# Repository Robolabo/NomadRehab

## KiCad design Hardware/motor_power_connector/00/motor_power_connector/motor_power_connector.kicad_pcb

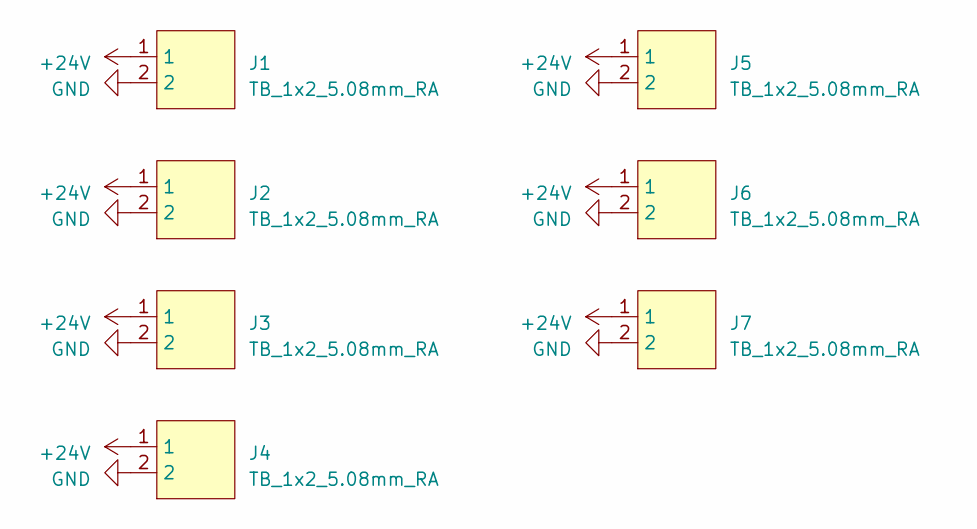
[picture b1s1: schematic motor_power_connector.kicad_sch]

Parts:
J1, J2, J3, J4, J5, J6, J7: TB_1x2_5.08mm_RA; MX2EDGR-5.08-GN01-02P-Cu-A; LCSC C5187973

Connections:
+24V: J1.1, J2.1, J3.1, J4.1, J5.1, J6.1, J7.1
GND: J1.2, J2.2, J3.2, J4.2, J5.2, J6.2, J7.2

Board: 2 copper layers, 9 parts (1 on the bottom side), 2 nets, no tracks yet.

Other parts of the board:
@Alejo2313, May 23: LOGO; dora_20x13
motor_power_connecto V0.0: LOGO; robolabo_40x15

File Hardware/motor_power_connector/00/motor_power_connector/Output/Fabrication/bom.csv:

Designator,Footprint,Quantity,Value,LCSC Part #
"_2, ",,2,,
"J1, J2, J3, J4, J5, J6, J7",MX2EDGR-5.08-GN01-02P-Cu-A,7,TB_1x2_5.08mm_RA,C5187973

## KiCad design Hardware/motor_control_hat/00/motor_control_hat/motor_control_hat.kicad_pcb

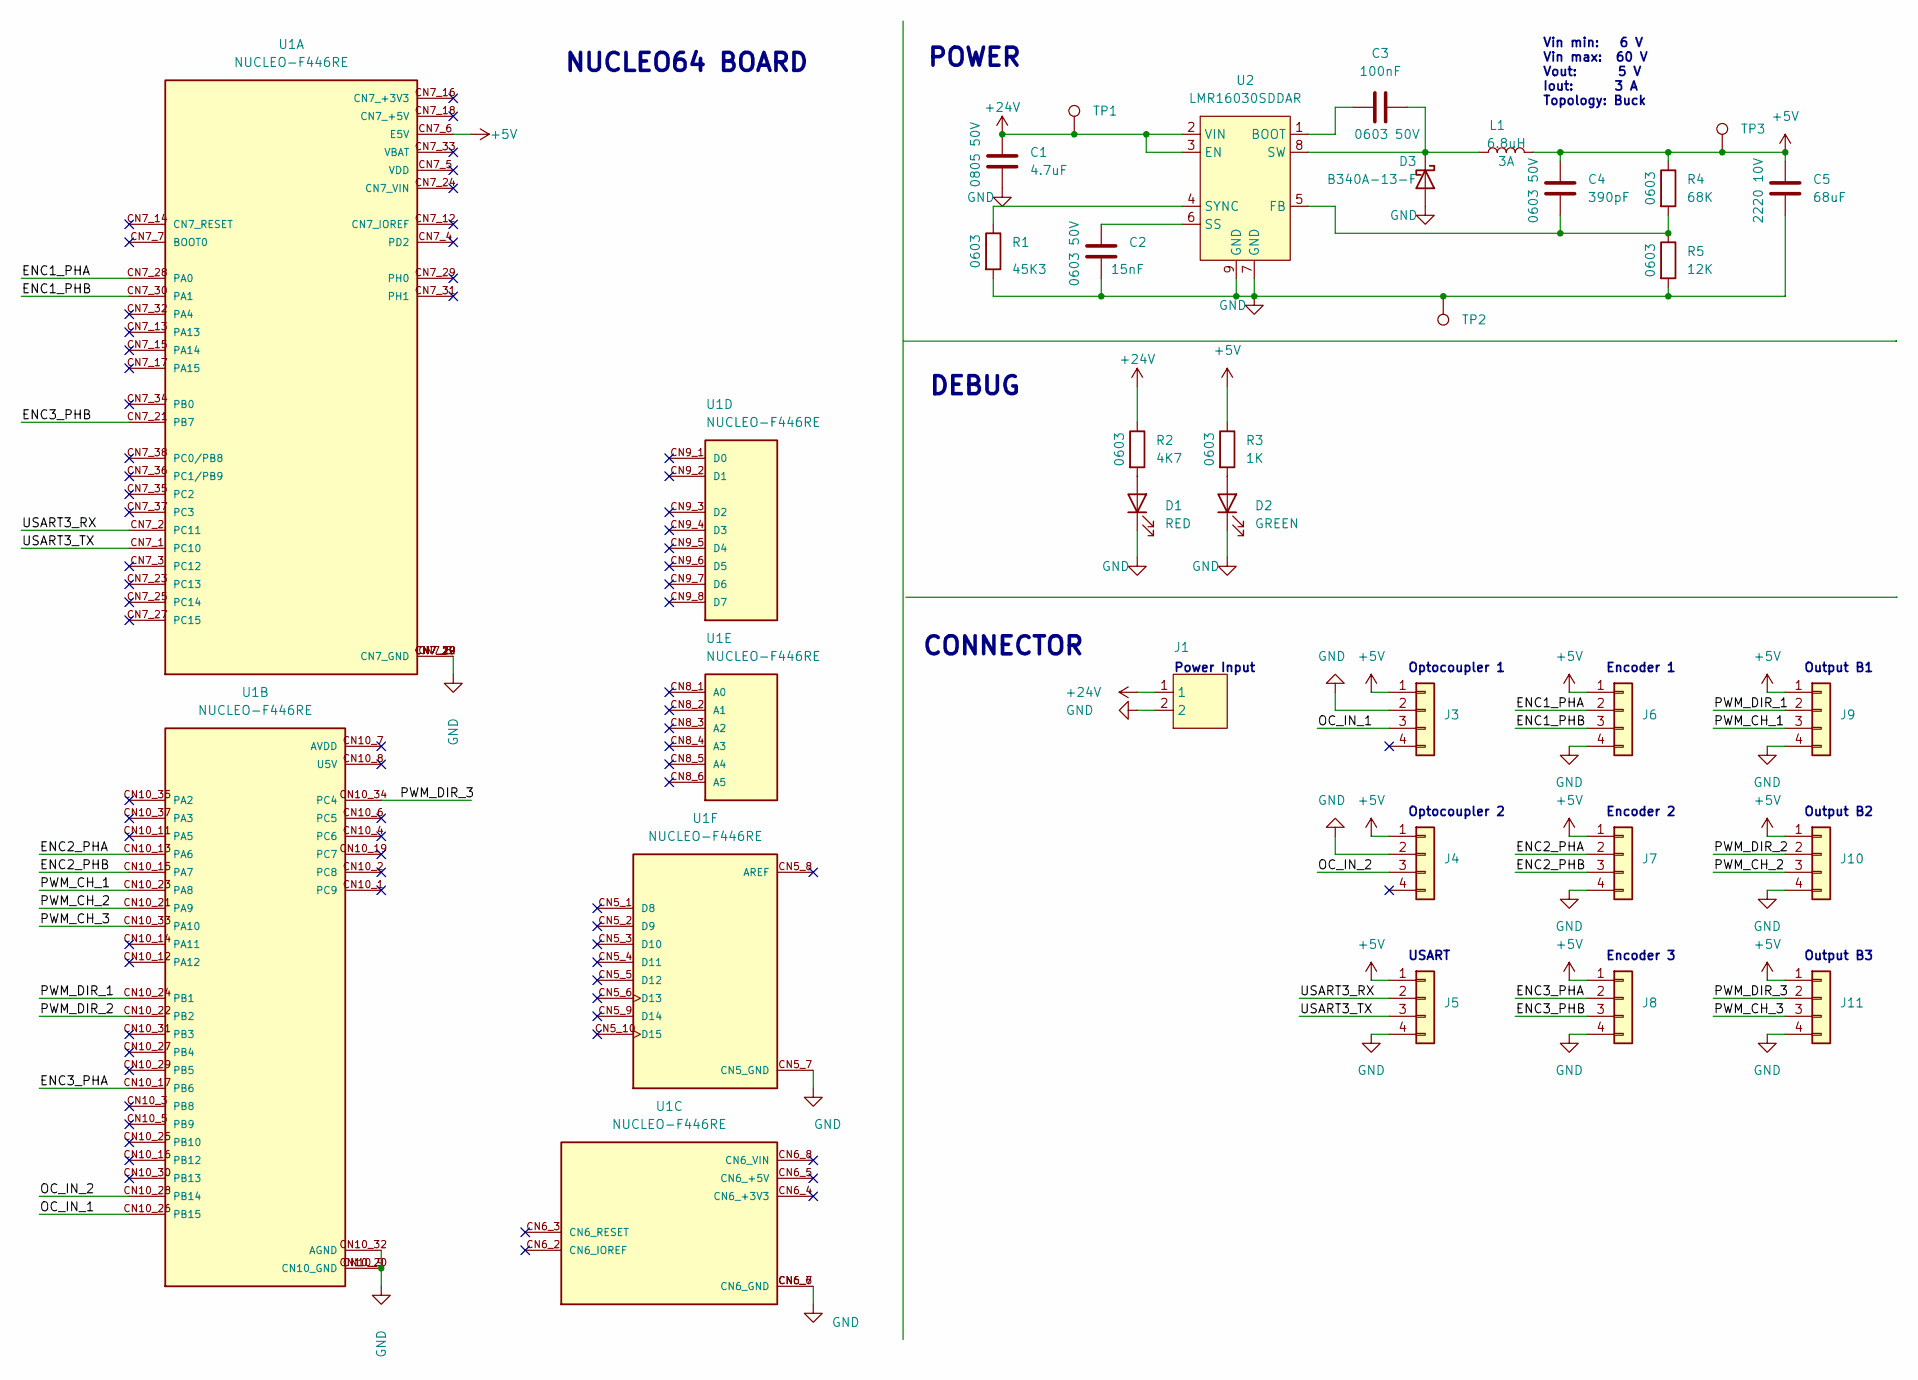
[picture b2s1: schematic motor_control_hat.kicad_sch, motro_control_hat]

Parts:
C1: 4.7uF; C_0805_2012Metric; Tolerance 20%; Voltage 50V; LCSC C98192
C2: 15nF; C_0603_1608Metric; Tolerance 20%; Voltage 50V; LCSC C107076
C3: 100nF; C_0603_1608Metric; Tolerance 20%; Voltage 50V; LCSC C14663
C4: 390pF; C_0603_1608Metric; Tolerance 10%; Voltage 50V; LCSC C107089
C5: 68uF; C_2220_5650Metric; Voltage 10V; Tolerance 20%; LCSC C342299
D1: RED; LED_0603_1608Metric; LCSC C84263
D2: GREEN; LED_0603_1608Metric; LCSC C84267
D3: B340A-13-F; D_SMA; LCSC C85098
J1: TB_1x2_5.08mm_RA; MX2EDGR-5.08-GN01-02P-Cu-A; LCSC C5187973
J3, J4, J5, J6, J7, J8, J9, J10, J11: S4B-XH-A(LF)(SN); JST_XH_S4B-XH-A_1x04_P2.50mm_Horizontal; LCSC C157925
L1: 6.8uH; L_Taiyo-Yuden_NR-60xx; Tolerance 20%; LCSC C192303
R1: 45K3; R_0603_1608Metric; Tolerance 1%; LCSC C245971
R2: 4K7; R_0603_1608Metric; Tolerance 1%; LCSC C99782
R3: 1K; R_0603_1608Metric; Tolerance 1%; LCSC C22548
R4: 68K; R_0603_1608Metric; Tolerance 1%; LCSC C114633
R5: 12K; R_0603_1608Metric; Tolerance 1%; LCSC C114659
TP1: +24V; TestPoint_Pad_D1.0mm; JLCPCB BOM 0
TP2: +5V_TP; TestPoint_Pad_D1.0mm; JLCPCB BOM 0
TP3: +5V; TestPoint_Pad_D1.0mm; JLCPCB BOM 0
U1: NUCLEO-F446RE; MODULE_NUCLEO-F446RE; PARTREV 13; JLCPCB BOM 0
U2: LMR16030SDDAR; VREG_LM5017MR_NOPB; LCSC C136648

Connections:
+5V: C4.1, C5.1, J3.1, J4.1, J5.1, J6.1, J7.1, J8.1, J9.1, J10.1, J11.1, L1.2, R3.1, R4.1, TP3.1, U1.CN7_6 (E5V)
+24V: C1.1, J1.1, R2.1, TP1.1, U2.2 (VIN), U2.3 (EN)
/ENC1_PHA: J6.2, U1.CN7_28 (PA0)
/ENC1_PHB: J6.3, U1.CN7_30 (PA1)
/ENC2_PHA: J7.2, U1.CN10_13 (PA6)
/ENC2_PHB: J7.3, U1.CN10_15 (PA7)
/ENC3_PHA: J8.2, U1.CN10_17 (PB6)
/ENC3_PHB: J8.3, U1.CN7_21 (PB7)
/OC_IN_1: J3.3, U1.CN10_26 (PB15)
/OC_IN_2: J4.3, U1.CN10_28 (PB14)
/PWM_CH_1: J9.3, U1.CN10_23 (PA8)
/PWM_CH_2: J10.3, U1.CN10_21 (PA9)
/PWM_CH_3: J11.3, U1.CN10_33 (PA10)
/PWM_DIR_1: J9.2, U1.CN10_24 (PB1)
/PWM_DIR_2: J10.2, U1.CN10_22 (PB2)
/PWM_DIR_3: J11.2, U1.CN10_34 (PC4)
/USART3_RX: J5.2, U1.CN7_2 (PC11)
/USART3_TX: J5.3, U1.CN7_1 (PC10)
GND: C1.2, C2.2, C5.2, D1.1 (K), D2.1 (K), D3.2 (A), J1.2, J3.2, J4.2, J5.4, J6.4, J7.4, J8.4, J9.4, J10.4, J11.4, R1.2, R5.2, TP2.1, U1.CN5_7 (CN5_GND), U1.CN6_6 (CN6_GND), U1.CN6_7 (CN6_GND), U1.CN7_8 (CN7_GND), U1.CN7_19 (CN7_GND), U1.CN7_20 (CN7_GND), U1.CN7_22 (CN7_GND), U1.CN10_9 (CN10_GND), U1.CN10_20 (CN10_GND), U1.CN10_32 (AGND), U2.7 (GND), U2.9 (GND), U2.10, U2.11, U2.12, U2.13, U2.14, U2.15, U2.16, U2.17
unnamed: D1.2 (A), R2.2
unnamed: D2.2 (A), R3.2
unnamed: C3.2, D3.1 (K), L1.1, U2.8 (SW)
unnamed: C3.1, U2.1 (BOOT)
unnamed: C4.2, R4.2, R5.1, U2.5 (FB)
unnamed: C2.1, U2.6 (SS)
unnamed: R1.1, U2.4 (SYNC)

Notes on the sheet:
DEBUG
Optocoupler 1
Vin min: 6 V Vin max: 60 V Vout: 5 V Iout: 3 A Topology: Buck
Output B1
Power Input
CONNECTOR
Encoder 2
POWER
Encoder 1
USART
Optocoupler 2
NUCLEO64 BOARD
Output B2
Output B3
Encoder 3

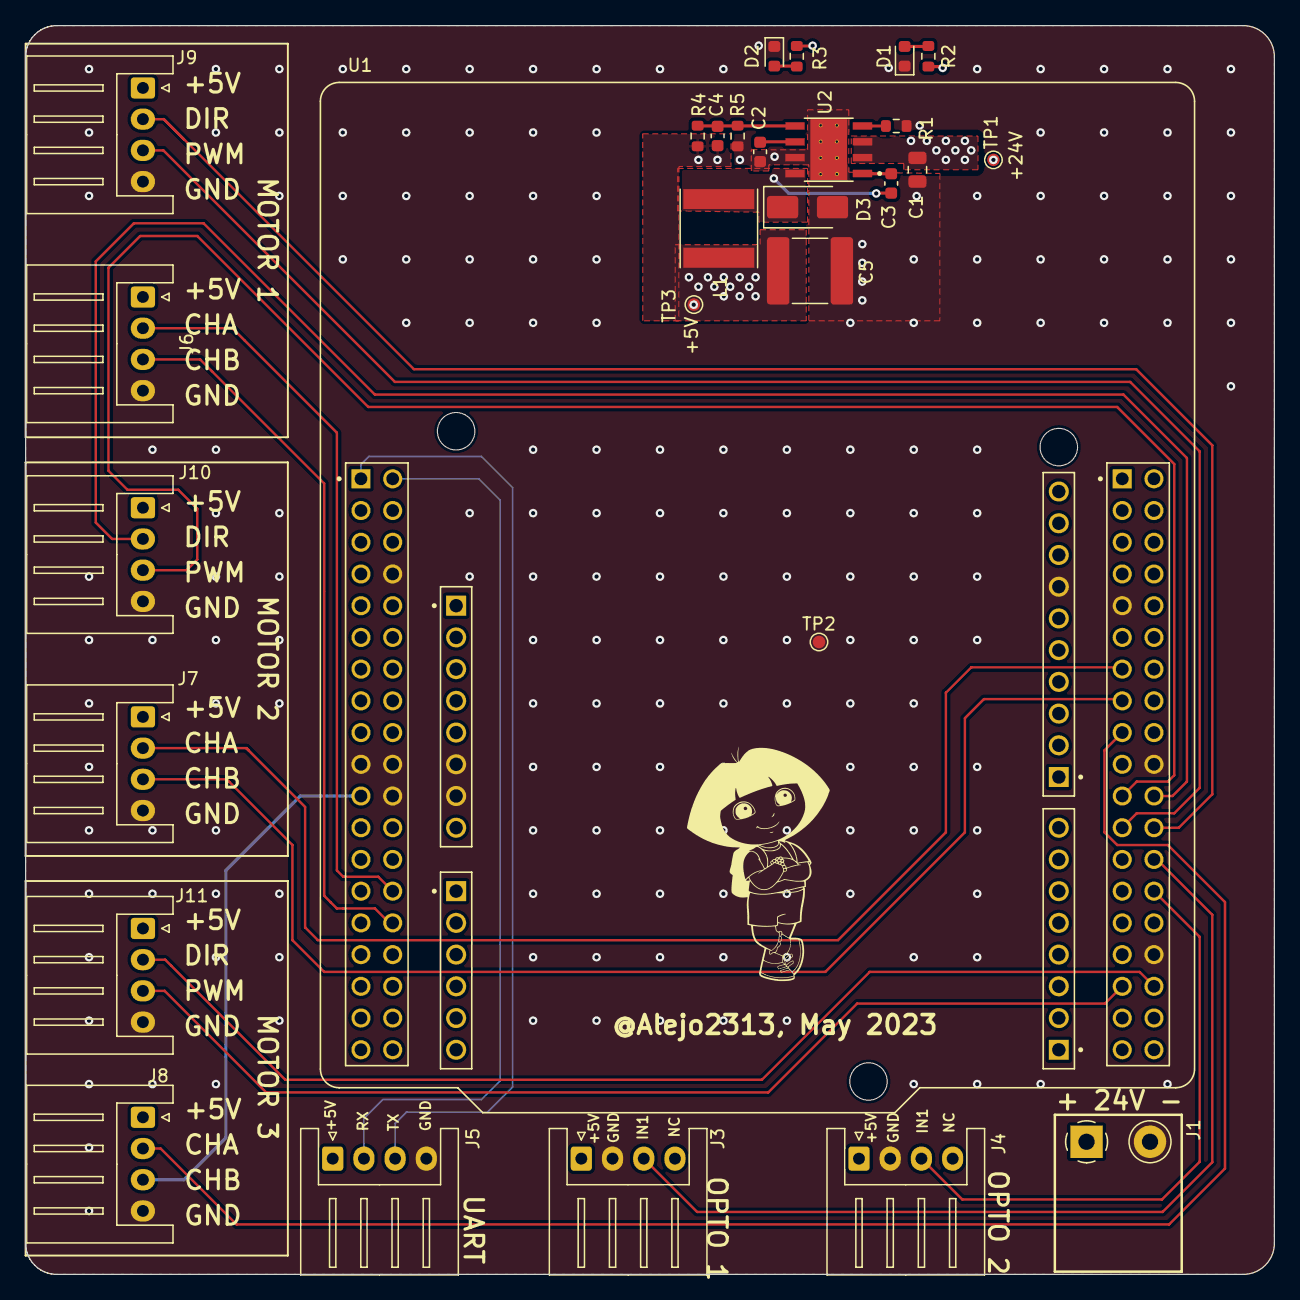
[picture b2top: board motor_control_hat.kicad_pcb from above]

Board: 4 copper layers, 100.0 x 100.0 mm, 31 parts (1 on the bottom side), 26 nets.

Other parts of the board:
@Alejo2313, May 2023: LOGO; dora_20x13
NomadMotorHat V0.0: LOGO; robolabo_87x33

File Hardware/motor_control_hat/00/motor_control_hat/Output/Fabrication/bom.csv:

Designator,Footprint,Quantity,Value,LCSC Part #
C1,0805,1,4.7uF,C98192
C2,0603,1,15nF,C107076
C3,0603,1,100nF,C14663
C4,0603,1,390pF,C107089
C5,2220,1,68uF,C342299
D1,0603,1,RED,C84263
D2,0603,1,GREEN,C84267
D3,D_SMA,1,B340A-13-F,C85098
J1,MX2EDGR-5.08-GN01-02P-Cu-A,1,TB_1x2_5.08mm_RA,C5187973
"J10, J11, J3, J4, J5, J6, J7, J8, J9",JST_XH_S4B-XH-A_1x04_P2.50mm_Horizontal,9,S4B-XH-A(LF)(SN),C157925
L1,L_Taiyo-Yuden_NR-60xx,1,6.8uH,C192303
R1,0603,1,45K3,C245971
R2,0603,1,4K7,C99782
R3,0603,1,1K,C22548
R4,0603,1,68K,C114633
R5,0603,1,12K,C114659
U1,MODULE_NUCLEO-F446RE,1,NUCLEO-F446RE,-
U2,VREG_LM5017MR_NOPB,1,LMR16030SDDAR,C136648

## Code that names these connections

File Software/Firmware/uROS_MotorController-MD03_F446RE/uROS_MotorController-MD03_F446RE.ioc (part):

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Mcu.Name=STM32F446R(C-E)Tx
Mcu.Package=LQFP64
Mcu.UserName=STM32F446RETx
PA0-WKUP.GPIOParameters=GPIO_PuPd,GPIO_Label
PA0-WKUP.GPIO_Label=ENC1_PHA
PA0-WKUP.GPIO_PuPd=GPIO_PULLUP
PA0-WKUP.Signal=S_TIM2_CH1_ETR
PA1.GPIOParameters=GPIO_PuPd,GPIO_Label
PA1.GPIO_Label=ENC1_PHB
PA1.GPIO_PuPd=GPIO_PULLUP
PA1.Signal=S_TIM2_CH2
PA10.GPIOParameters=GPIO_Label
PA10.GPIO_Label=PWM_CH_3
PA10.Signal=S_TIM1_CH3
PA13.GPIOParameters=GPIO_Label
PA13.GPIO_Label=TMS
PA13.Mode=Serial_Wire
PA13.Signal=SYS_JTMS-SWDIO
PA14.GPIOParameters=GPIO_Label
PA14.GPIO_Label=TCK
PA14.Mode=Serial_Wire
PA14.Signal=SYS_JTCK-SWCLK
PA2.GPIOParameters=GPIO_Label
PA2.GPIO_Label=USART_TX
PA2.Mode=Asynchronous
PA2.Signal=USART2_TX
PA3.GPIOParameters=GPIO_Label
PA3.GPIO_Label=USART_RX
PA3.Mode=Asynchronous
PA3.Signal=USART2_RX
PA5.GPIOParameters=GPIO_Label
PA5.GPIO_Label=LD2 [Green Led]
PA5.Signal=GPIO_Output
PA6.GPIOParameters=GPIO_PuPd,GPIO_Label
PA6.GPIO_Label=ENC2_PHA
PA6.GPIO_PuPd=GPIO_PULLUP
PA6.Signal=S_TIM3_CH1
PA7.GPIOParameters=GPIO_PuPd,GPIO_Label
PA7.GPIO_Label=ENC2_PHB
PA7.GPIO_PuPd=GPIO_PULLUP
PA7.Signal=S_TIM3_CH2
PA8.GPIOParameters=GPIO_Label
PA8.GPIO_Label=PWM_CH_1
PA8.Signal=S_TIM1_CH1
PA9.GPIOParameters=GPIO_Label
PA9.GPIO_Label=PWM_CH_2
PA9.Signal=S_TIM1_CH2
PB1.GPIOParameters=GPIO_Label
PB1.GPIO_Label=PWM_DIR_1
PB1.Signal=GPIO_Output
PB2.GPIOParameters=GPIO_Label
PB2.GPIO_Label=PWM_DIR_2
PB2.Signal=GPIO_Output
PB3.GPIOParameters=GPIO_Label
PB3.GPIO_Label=SWO
PB3.Signal=SYS_JTDO-SWO
PB6.Signal=S_TIM4_CH1
PB7.Signal=S_TIM4_CH2
PB8.GPIOParameters=GPIO_Pu
PB8.GPIO_Pu=GPIO_PULLUP
PB8.Mode=I2C
PB8.Signal=I2C1_SCL
PB9.GPIOParameters=GPIO_Pu
PB9.GPIO_Pu=GPIO_PULLUP
PB9.Mode=I2C
PB9.Signal=I2C1_SDA
PC10.Mode=Asynchronous
PC10.Signal=USART3_TX
PC11.Mode=Asynchronous
PC11.Signal=USART3_RX
PC13.GPIOParameters=GPIO_Label,GPIO_ModeDefaultEXTI
PC13.GPIO_Label=B1 [Blue PushButton]
PC13.GPIO_ModeDefaultEXTI=GPIO_MODE_IT_FALLING
PC13.Signal=GPXTI13
PC14-OSC32_IN.Mode=LSE-External-Oscillator
PC14-OSC32_IN.Signal=RCC_OSC32_IN
PC15-OSC32_OUT.Mode=LSE-External-Oscillator
PC15-OSC32_OUT.Signal=RCC_OSC32_OUT
PC4.GPIOParameters=GPIO_Label
PC4.GPIO_Label=PWM_DIR_3
PC4.Signal=GPIO_Output
PH0-OSC_IN.Mode=HSE-External-Oscillator
PH0-OSC_IN.Signal=RCC_OSC_IN
PH1-OSC_OUT.Mode=HSE-External-Oscillator
PH1-OSC_OUT.Signal=RCC_OSC_OUT
RCC.HSE_VALUE=8000000
RCC.SYSCLKFreq_VALUE=180000000
RCC.SYSCLKSource=RCC_SYSCLKSOURCE_PLLCLK
board=NUCLEO-F446RE
boardIOC=true

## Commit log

2022-10-28 Initial uros application created
2022-10-29 Sonar driver integrated
2022-10-30 uROS sonar application added
2022-11-05 Multi-node application created!
2022-11-05 CPU frequency increased to 216 MHz
2022-11-07 Sonar driver working with freeRTOS
2022-11-10 MD03 motor driver created
2022-11-17 PWM driver created
2022-11-21 uROS application created
2022-11-27 Encoder driver created
2023-02-12 Initial encoder driver created!
2023-02-13 Encoder test created
2023-02-15 PID controller created
2023-02-17 Project restructured
2023-02-19 Rotatory base controller created
2023-02-20 Comments added, unused headers removed
2023-02-20 uROS motor task created
2023-02-21 uROS app working
2023-02-21 Context store featured added
2023-02-22 Base rotation controller context storage added
2023-02-26 Speed controlled tested with real motors
2023-03-06 Message types updated
2023-03-08 Wheel controller rotation controller parameters updated
2023-03-09 Wheel odom created
2023-03-10 Unnecessary publishers removed. Topics renammed
2023-03-17 initial URDF model created
2023-03-25 feat: Nomad ROS2 dockerfile created
    Dockerfile with:
    * Ubuntu 22.04
    * ROS 2 Humble
    * Ignition Gazebo Fortress
2023-03-25 feat: ROS2 pkg for the nomad200 robot simulation created
    Initial structure for the simulation pkg (gazebo & rviz)
2023-05-03 Initial PCB created
2023-05-06 Motor hat V0 created
2023-05-08 Power connectors removed
2023-05-09 Connectors changed. New power distribution board
2023-07-29 feat: imu sensor added
    imu model & plugin (gazebo & rviz)
2023-10-04 New robot model created
2023-10-05 Synchro-drive controller created
2023-10-05 joy controller added!
2023-10-07 Motor communications refactored
2023-10-08 Hardware interface working!
2023-10-10 Transform issue solved!
2023-10-11 Added sonar and IR description
2023-10-21 sensor emulator updated
2023-10-21 Syncro-drive controller updated
